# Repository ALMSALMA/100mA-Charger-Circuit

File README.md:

# 100mA-Charger-Circuit

a 100mA charger circuit was designed in LTSpice and then the schematic and PCB of the circuit was designed in EAGLE.

The designed circuit:

Schematic in EAGLE:

PCB in EAGLE:

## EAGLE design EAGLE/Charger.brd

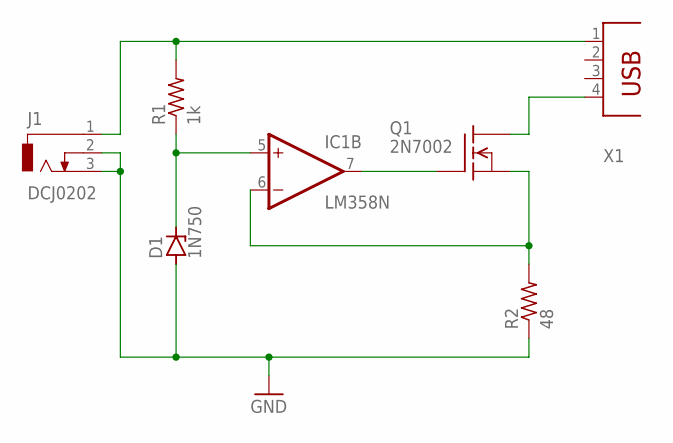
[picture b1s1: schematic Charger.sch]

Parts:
D1: 1N750; DO35Z10
IC1: LM358N; DIL08
J1: DCJ0202
Q1: 2N7002; TO-92
R1: 1k; 0204/7
R2: 48; 0204/7
X1: PN87520

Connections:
GND: D1.A, IC1.4 (V-), J1.2, J1.3, R2.1
unnamed: IC1.6 (-IN), Q1.1 (S), R2.2
unnamed: D1.C, IC1.5 (+IN), R1.1
unnamed: IC1.7 (OUT), Q1.2 (G)
unnamed: Q1.3 (D), X1.4
V+: IC1.8 (V+), J1.1, R1.2, X1.1

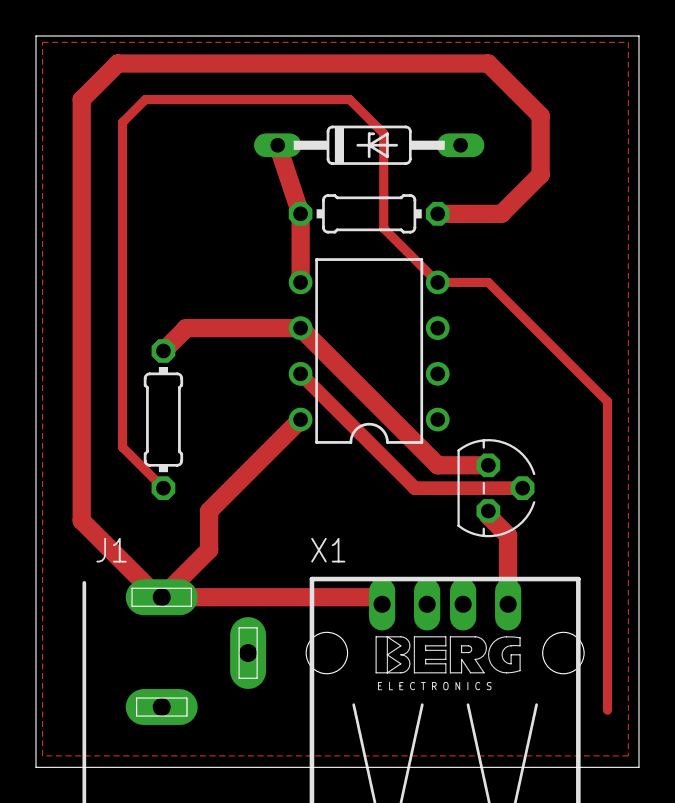
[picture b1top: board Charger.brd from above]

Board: 2 copper layers, 33.5 x 40.6 mm, 7 parts (0 on the bottom side), 6 nets.
